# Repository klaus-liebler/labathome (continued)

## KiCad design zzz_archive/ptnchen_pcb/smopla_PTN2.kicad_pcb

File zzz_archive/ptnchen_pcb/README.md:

# smopla_PTN2 - "Das kleine Peteh Ennchen"

Der kleine Bruder von lab@home. Ermöglicht das Experimentieren mit PT1...PTn-Gliedern, die intern als RC-Kombination (entkoppelt über Operationsverstärker) ausgeführt sind.
Features:
- Drei hintereinander geschaltete RC-Glieder, die bekanntlich PT1-Verhalten aufweisen; bilden eine Regelstrecke
- WIFI-fähiger Microcontroller (ESP32)
- Webbasierte Schnittstelle
- bald: Schnittstelle zu WinFACT Boris über WiFi
- Anregung über mechanischen Schalter oder softwaregesteurert über den Microcontroller
- Jedes PT1-Glied kann mit einstellbarer Intensität gestört werden
- Technisch: Anregungsspannung und Spannungen am Ausgang der RC-Glieder über Laborstecker herausgeführt und auf Analog-Digital-Wandler geführt
- Fachlich: Spannungen sind über externe Messinstrumente messbar oder stehen auf der Weboberfläche zur Verfügung oder stehen in einem BORIS-Funktionsbaustein zur Verfügung
- Softwareseitig kann der Regelkreis geöffnet oder geschlossen werden. Es stehen verschiedene Reglertypen und Parametersets zur Verfügung
- Die Verstärker zur Entkopplung der PT1-Glieder lassen sich mechanisch aktivieren und deaktivieren (dann keine Rückkopplungsfreiheit)
- Farbige LEDs zeigen den Zustand des Gesamtsystems und der einzelnen PT1-Glieder an
- Spannungsversorgung, Programmierung und bei Bedarf auch Kommunikation über USB-C

Ein Bild der Baugruppe sagt mehr, als tausend Worte

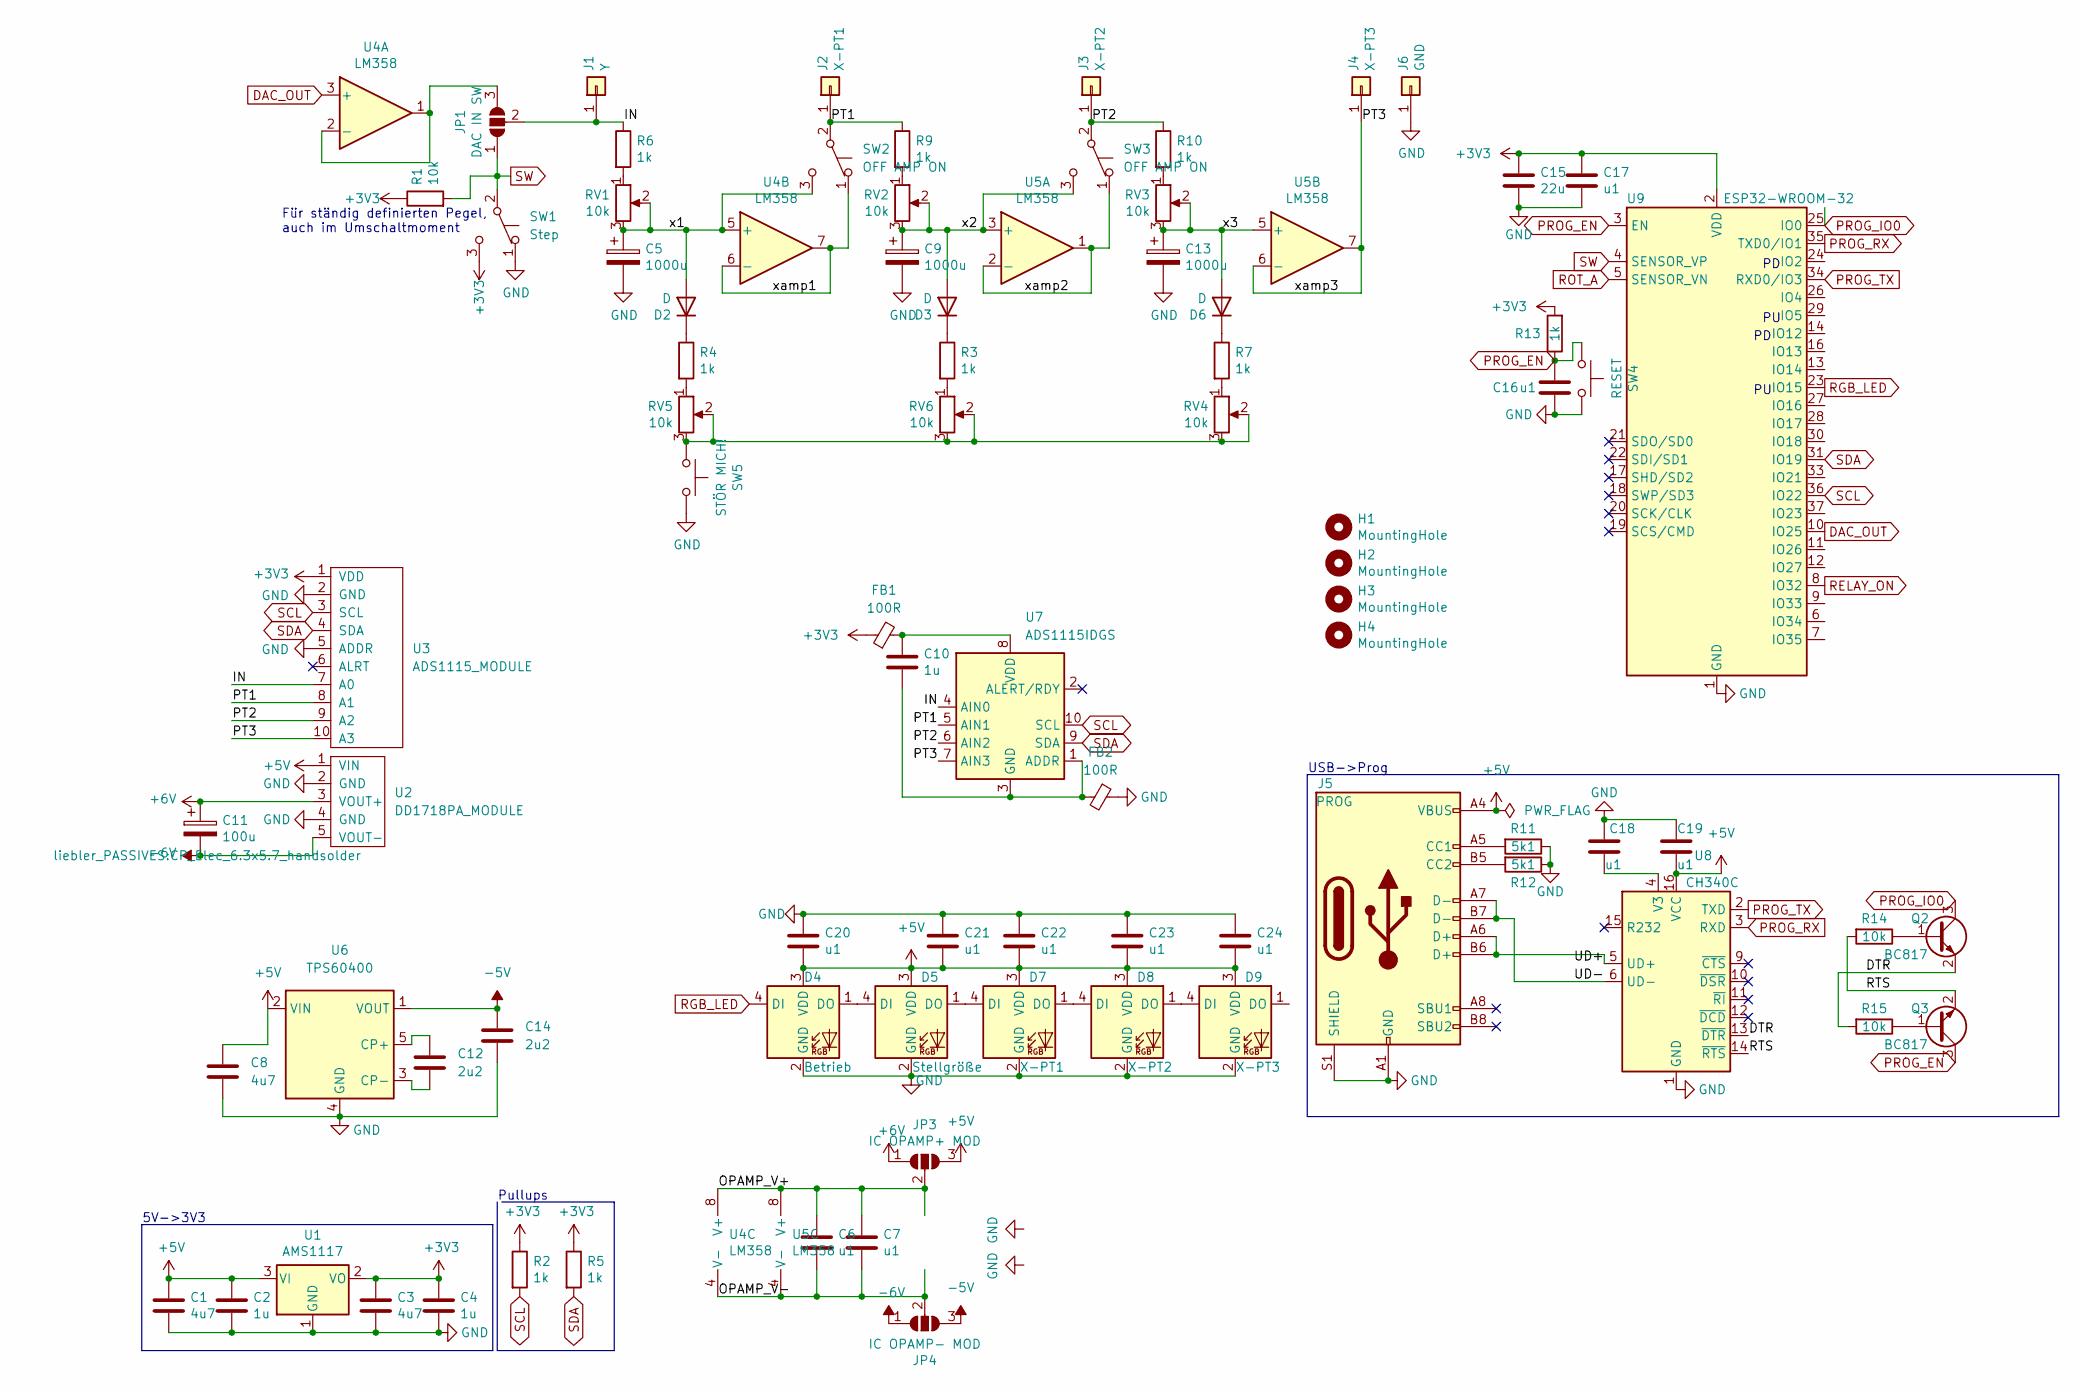
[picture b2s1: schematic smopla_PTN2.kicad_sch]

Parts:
C1, C3, C8: 4u7; C_0805_2012Metric_Pad1.18x1.45mm_HandSolder
C2, C4, C10: 1u; C_0805_2012Metric_Pad1.18x1.45mm_HandSolder
C5, C9, C13: 1000u; CP_Elec_10x10_handsolder; JLCPCB C280409
C6, C7, C16, C17, C18, C19, C20, C21, C22, C23, C24: u1; C_0805_2012Metric_Pad1.18x1.45mm_HandSolder
C11: 100u; CP_Elec_6.3x5.7_handsolder
C12, C14: 2u2; C_0805_2012Metric_Pad1.18x1.45mm_HandSolder
C15: 22u; C_0805_2012Metric_Pad1.18x1.45mm_HandSolder
D2, D3, D6: D; D_SOD-123_handsolder
D4: Betrieb; LED_D5.0mm-4_RGB_Staggered_Pins
D5: Stellgröße; LED_D5.0mm-4_RGB_Staggered_Pins
D7: X-PT1; LED_D5.0mm-4_RGB_Staggered_Pins
D8: X-PT2; LED_D5.0mm-4_RGB_Staggered_Pins
D9: X-PT3; LED_D5.0mm-4_RGB_Staggered_Pins
FB1, FB2: 100R; L_0805_2012Metric_Pad1.05x1.20mm_HandSolder
H1, H2, H3, H4: MountingHole; MountingHole_3.2mm_M3_DIN965
J1: Y; Banana_RECESSED
J2: X-PT1; Banana_RECESSED
J3: X-PT2; Banana_RECESSED
J4: X-PT3; Banana_RECESSED
J5: PROG; USB_C_Receptacle_HRO_TYPE-C-31-M-12_IMPROVED
J6: GND; Banana_RECESSED
JP1: DAC IN SW; SolderJumper-3_P1.3mm_Open_RoundedPad1.0x1.5mm_NumberLabels
JP3: IC OPAMP+ MOD; SolderJumper-3_P1.3mm_Open_RoundedPad1.0x1.5mm_NumberLabels
JP4: IC OPAMP- MOD; SolderJumper-3_P1.3mm_Open_RoundedPad1.0x1.5mm_NumberLabels
Q2, Q3: BC817; SOT-23_Handsoldering
R1, R14, R15: 10k; R_0805_2012Metric_Pad1.20x1.40mm_HandSolder
R2, R3, R4, R5, R6, R7, R9, R10, R13: 1k; R_0805_2012Metric_Pad1.20x1.40mm_HandSolder
R11, R12: 5k1; R_0805_2012Metric_Pad1.20x1.40mm_HandSolder
RV1, RV2, RV3: 10k; Potentiometer_Alps_RK09K_Single_Vertical
RV4, RV5, RV6: 10k; Potentiometer_Bourns_3386P_Vertical
SW1: Step; MTS-102_recessed
SW2, SW3: OFF AMP ON; Switch_SS12D00
SW4: RESET; SW_SPST_TL3342
SW5: STÖR MICH!; Button_12mm_ANCHOR_CENTER
U1: AMS1117; SOT-223-3_TabPin2_HANDSOLDER
U2: DD1718PA_MODULE; DD1718PA_MODULE_SMD
U3: ADS1115_MODULE; ADS1115_MODULE_SMD
U4, U5: LM358; SOIC-8_3.9x4.9mm_Pitch1.27mm_handsolder
U6: TPS60400; SOT-23-5
U7: ADS1115IDGS; TSSOP-10_3x3mm_P0.5mm
U8: CH340C; SOIC-16_3.9x9.9mm_P1.27mm
U9: ESP32-WROOM-32

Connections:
+3V3: C3.2, C4.1, C15.1, C17.2, FB1.1, R1.1, R2.1, R5.1, R13.2, SW1.3 (C), U1.2 (VO), U3.1 (VDD), U9.2 (VDD)
+5V: C1.2, C2.1, C8.1, C19.1, C20.2, C21.2, C22.2, C23.2, C24.2, D4.3 (VDD), D5.3 (VDD), D7.3 (VDD), D8.3 (VDD), D9.3 (VDD), J5.A4 (VBUS), J5.A9 (VBUS), J5.B4 (VBUS), J5.B9 (VBUS), JP3.3 (B), U1.3 (VI), U2.1 (VIN), U6.2 (VIN), U8.16 (VCC)
+6V: C11.1, JP3.1 (A), U2.3 (VOUT+)
-5V: C14.1, JP4.3 (B), U6.1 (VOUT)
-6V: C11.2, JP4.1 (A), U2.5 (VOUT-)
/DTR: Q2.2 (E), R15.2, U8.13 (~DTR)
/IN: J1.1, JP1.2 (C), R6.1, U3.7 (A0), U7.4 (AIN0)
/OPAMP_V+: C6.1, C7.1, JP3.2 (C), U4.8 (V+), U5.8 (V+)
/OPAMP_V-: C6.2, C7.2, JP4.2 (C), U4.4 (V-), U5.4 (V-)
/PT1: J2.1, R9.1, SW2.2 (B), U3.8 (A1), U7.5 (AIN1)
/PT2: J3.1, R10.1, SW3.2 (B), U3.9 (A2), U7.6 (AIN2)
/PT3: J4.1, U3.10 (A3), U5.6 (-), U5.7, U7.7 (AIN3)
/RTS: Q3.2 (E), R14.2, U8.14 (~RTS)
/UD+: J5.A6 (D+), J5.B6 (D+), U8.5 (UD+)
/UD-: J5.A7 (D-), J5.B7 (D-), U8.6 (UD-)
/x1: C5.1, D2.2 (A), RV1.2, RV1.3, SW2.3 (C), U4.5 (+)
/x2: C9.1, D3.2 (A), RV2.2, RV2.3, SW3.3 (C), U5.3 (+)
/x3: C13.1, D6.2 (A), RV3.2, RV3.3, U5.5 (+)
/xamp1: SW2.1 (A), U4.6 (-), U4.7
/xamp2: SW3.1 (A), U5.1, U5.2 (-)
DAC_OUT: U4.3 (+), U9.10 (IO25)
GND: C1.1, C2.2, C3.1, C4.2, C5.2, C8.2, C9.2, C13.2, C14.2, C15.2, C16.1, C17.1, C18.2, C19.2, C20.1, C21.1, C22.1, C23.1, C24.1, D4.2 (GND), D5.2 (GND), D7.2 (GND), D8.2 (GND), D9.2 (GND), FB2.1, J5.A1 (GND), J5.A12 (GND), J5.B1 (GND), J5.B12 (GND), J5.S1 (SHIELD), J6.1, R11.1, R12.1, SW1.1 (A), SW4.2, SW5.2, U1.1 (GND), U2.2 (GND), U2.4 (GND), U3.2 (GND), U3.5 (ADDR), U6.4 (GND), U8.1 (GND), U9.1 (GND), U9.15 (GND), U9.38 (GND), U9.39 (GND)
unnamed: C10.1, FB2.2, U7.1 (ADDR), U7.3 (GND)
unnamed: C10.2, FB1.2, U7.8 (VDD)
unnamed: C12.1, U6.5 (CP+)
unnamed: C12.2, U6.3 (CP-)
unnamed: C18.1, U8.4 (V3)
unnamed: D2.1 (K), R4.1
unnamed: D3.1 (K), R3.1
unnamed: D4.1 (DO), D5.4 (DI)
unnamed: D5.1 (DO), D7.4 (DI)
unnamed: D6.1 (K), R7.1
unnamed: D7.1 (DO), D8.4 (DI)
unnamed: D8.1 (DO), D9.4 (DI)
unnamed: J5.A5 (CC1), R11.2
unnamed: J5.B5 (CC2), R12.2
unnamed: JP1.3 (B), U4.1, U4.2 (-)
unnamed: Q2.1 (B), R14.1
unnamed: Q3.1 (B), R15.1
unnamed: R3.2, RV6.1
unnamed: R4.2, RV5.1
unnamed: R6.2, RV1.1
unnamed: R7.2, RV4.1
unnamed: R9.2, RV2.1
unnamed: R10.2, RV3.1
unnamed: RV4.2, RV4.3, RV5.2, RV5.3, RV6.2, RV6.3, SW5.1
PROG_EN: C16.2, Q3.3 (C), R13.1, SW4.1, U9.3 (EN)
PROG_IO0: Q2.3 (C), U9.25 (IO0)
PROG_RX: U8.3 (RXD), U9.35 (TXD0/IO1)
PROG_TX: U8.2 (TXD), U9.34 (RXD0/IO3)
RELAY_ON: U9.8 (IO32)
RGB_LED: D4.4 (DI), U9.23 (IO15)
ROT_A: U9.5 (SENSOR_VN)
SCL: R2.2, U3.3 (SCL), U7.10 (SCL), U9.36 (IO22)
SDA: R5.2, U3.4 (SDA), U7.9 (SDA), U9.31 (IO19)
SW: JP1.1 (A), R1.2, SW1.2 (B), U9.4 (SENSOR_VP)

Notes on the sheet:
USB->Prog
Für ständig definierten Pegel, auch im Umschaltmoment
5V->3V3
Pullups

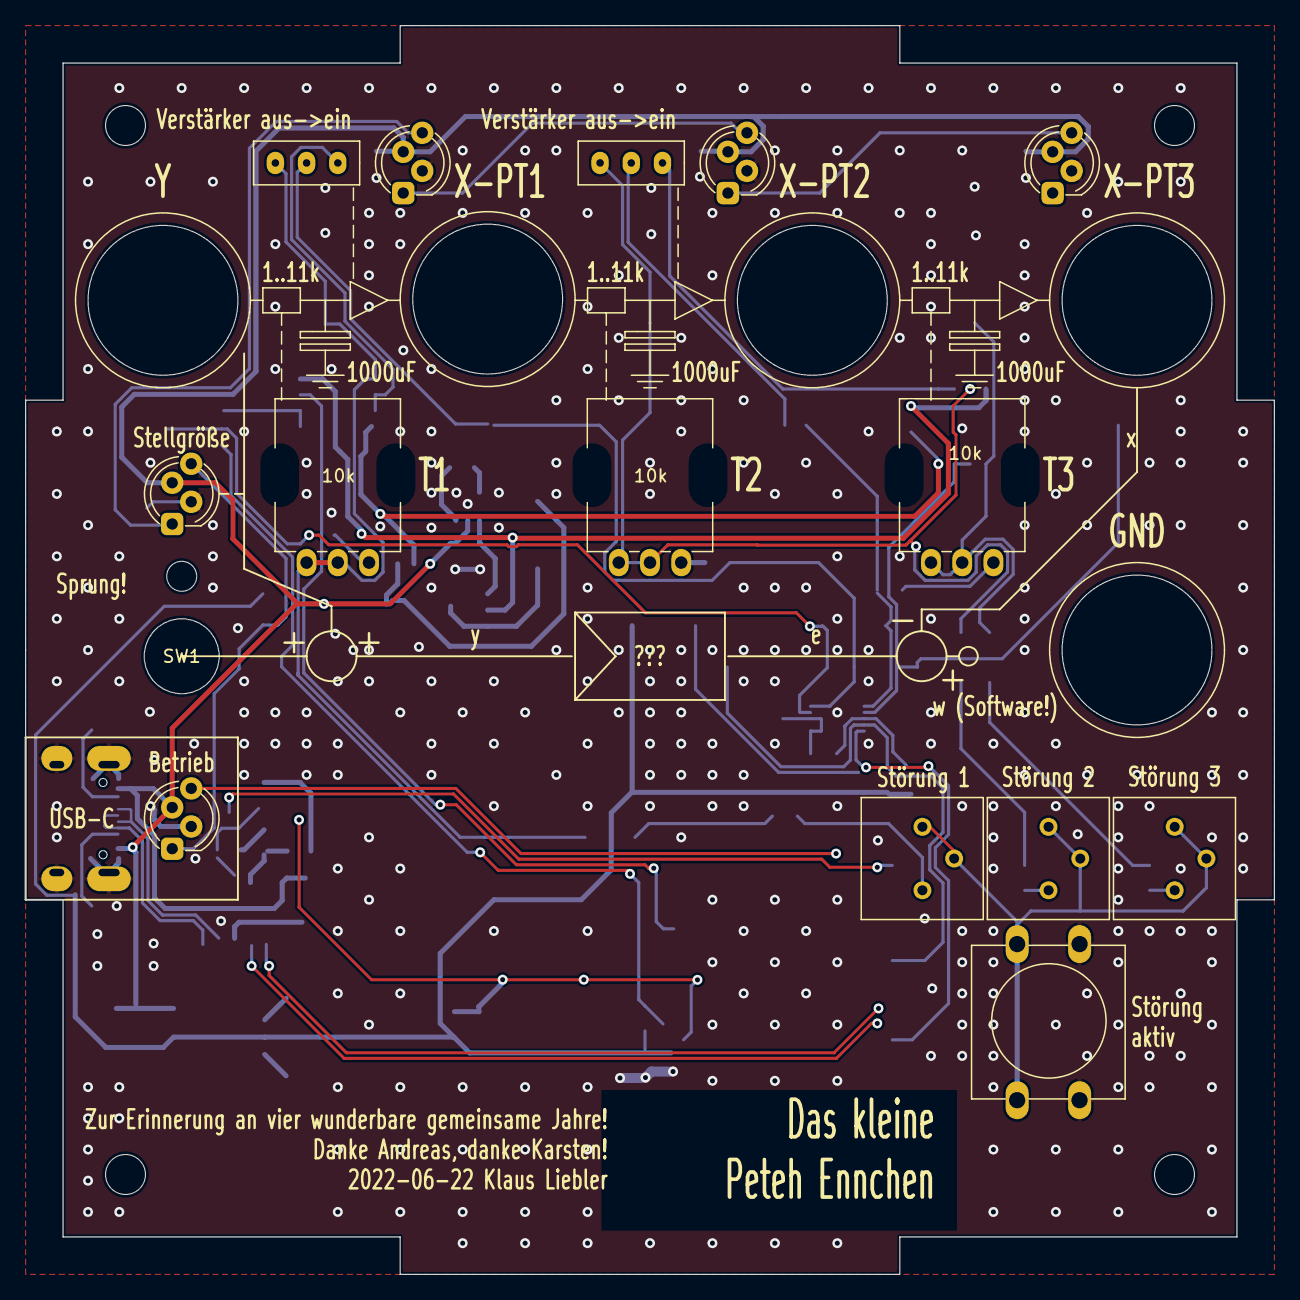
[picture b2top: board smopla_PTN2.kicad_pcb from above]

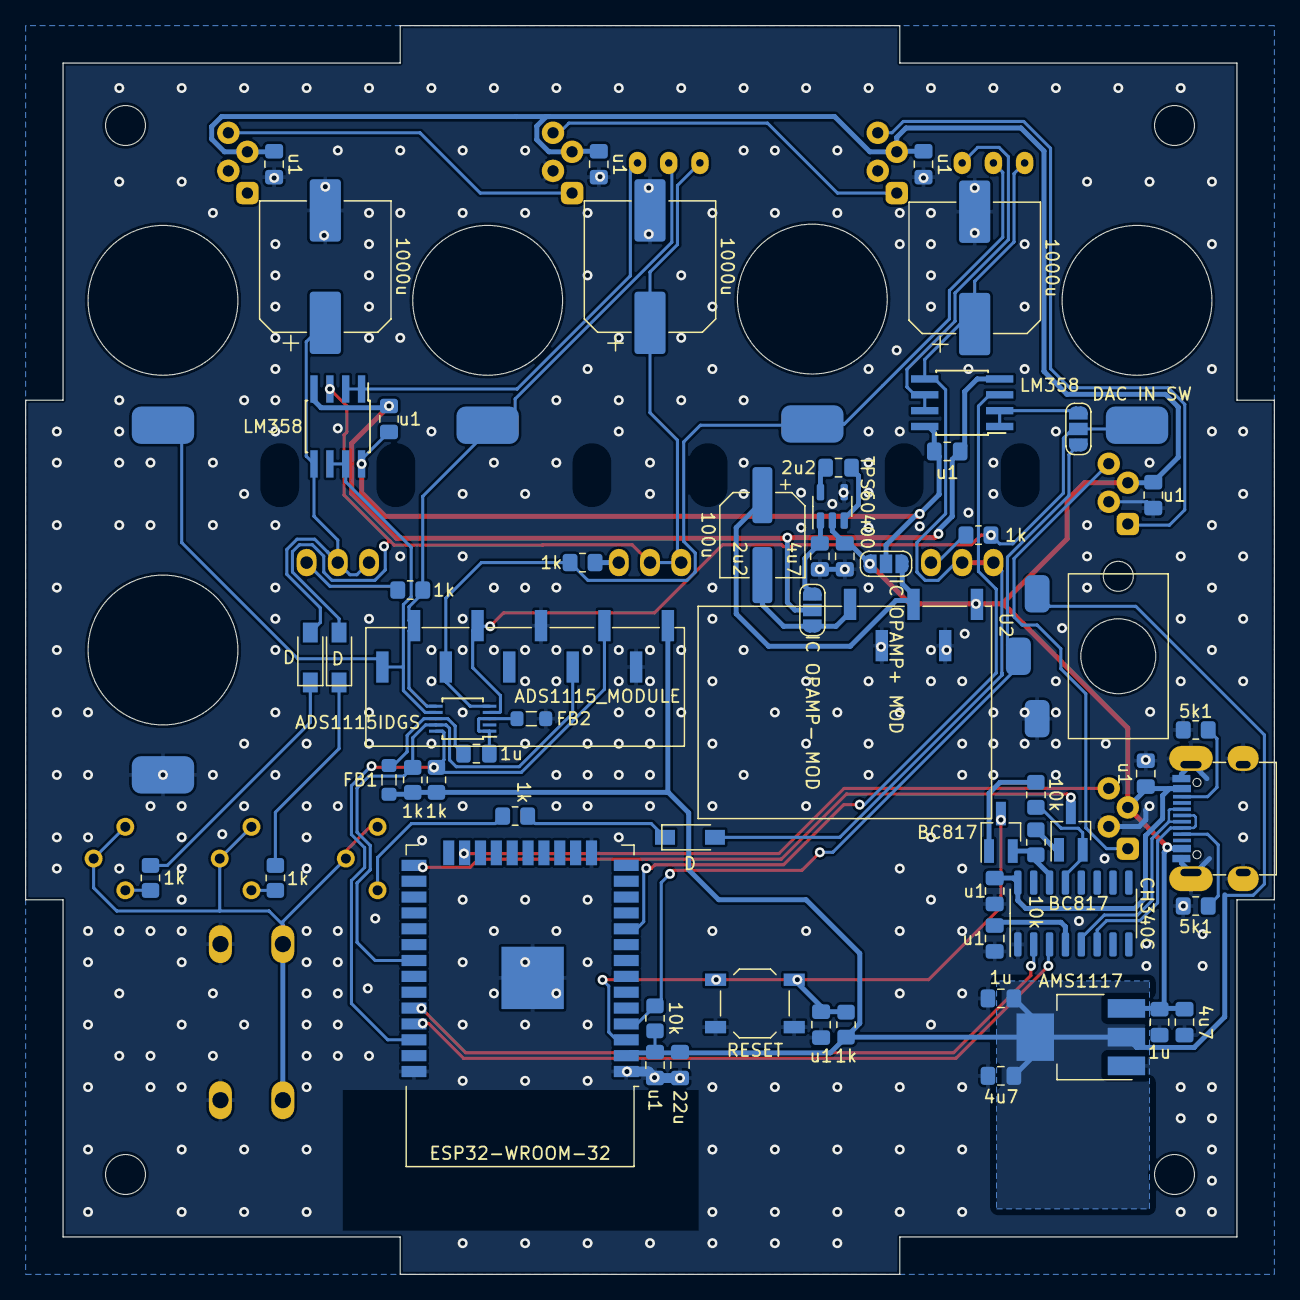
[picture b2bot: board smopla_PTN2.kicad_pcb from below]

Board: 2 copper layers, 100.0 x 100.0 mm, 83 parts (59 on the bottom side), 54 nets.

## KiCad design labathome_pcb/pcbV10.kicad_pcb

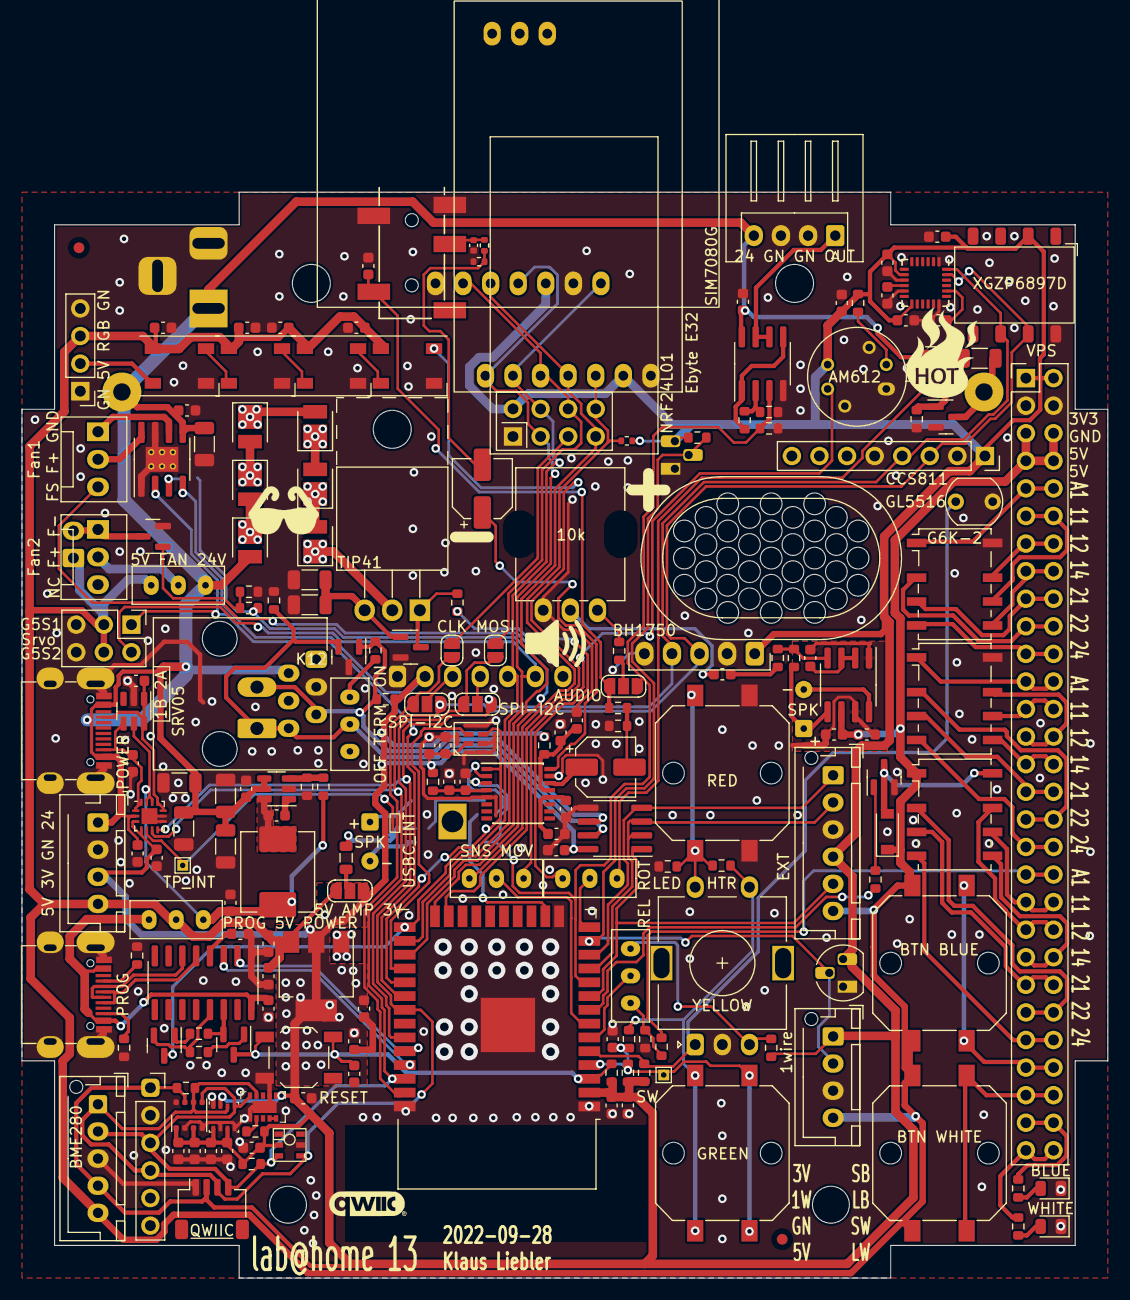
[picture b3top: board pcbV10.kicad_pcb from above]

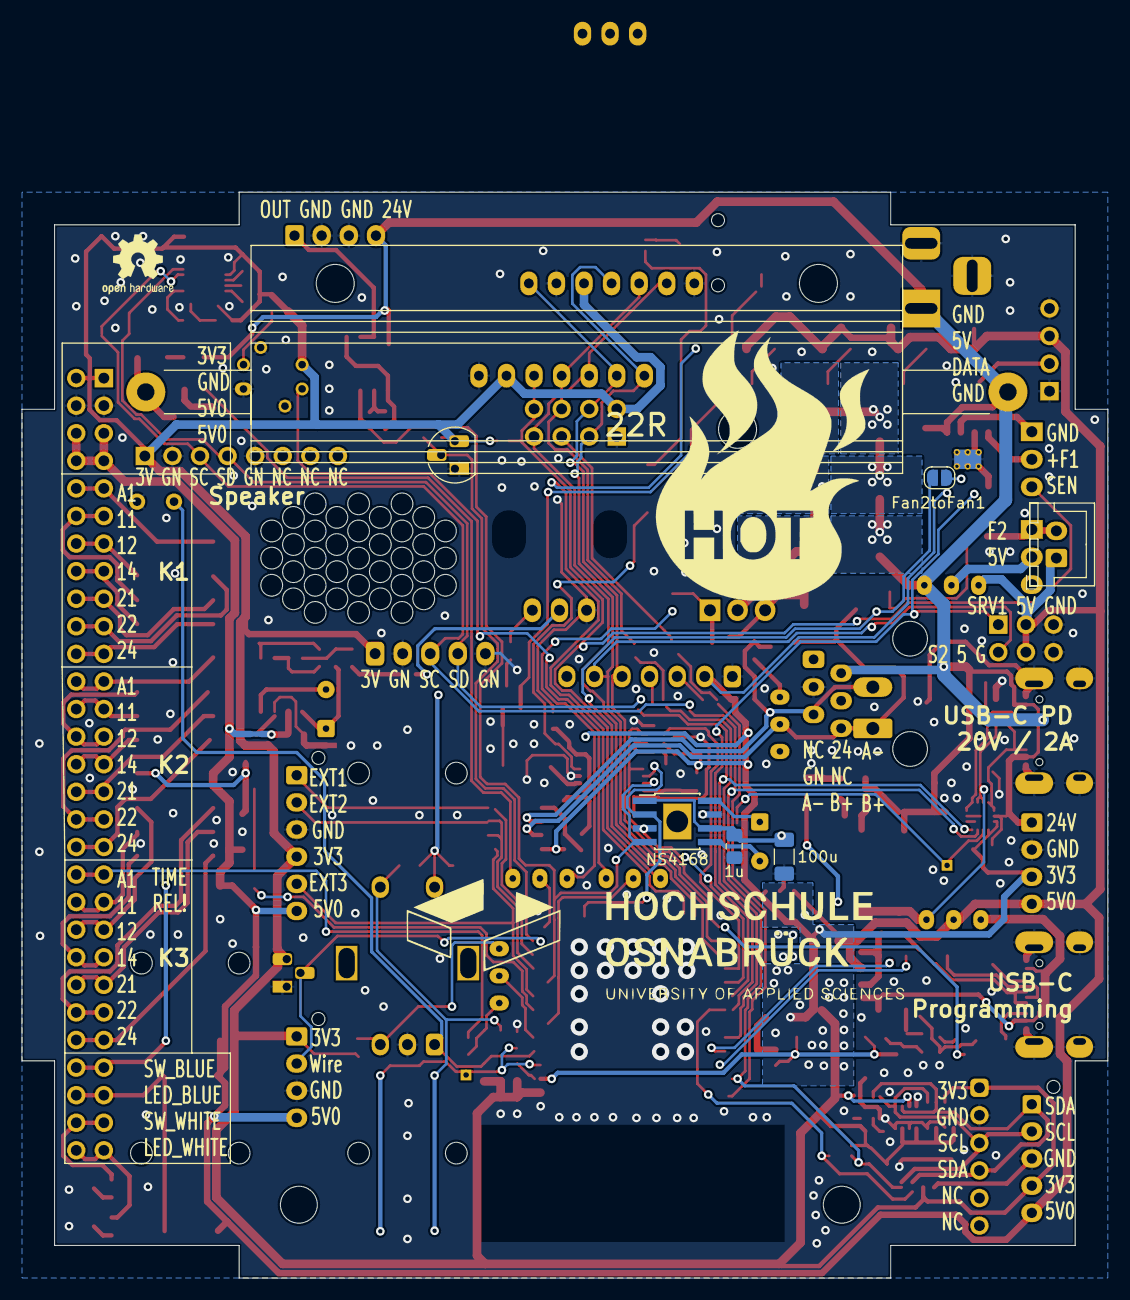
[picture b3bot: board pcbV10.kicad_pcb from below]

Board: 2 copper layers, 100.0 x 100.0 mm, 221 parts (12 on the bottom side), 144 nets.

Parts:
C1, C8: 4u7; C_0603_1608Metric
C2, C36, C47: 22u; C_0603_1608Metric
C3, C9, C23, C38: 1u; C_0603_1608Metric
C4, C5, C6, C7, C10, C11, C12, C14, C15, C16, C18, C19, C20, C24, C25, C28, C29, C30, C31, C32, C33, C35, C37, C40, C42, C44, C51, C52, C54, C55: u1; C_0603_1608Metric
C13, C43: 47u; C_0603_1608Metric
C17, C58: 1u; C_1206_3216Metric
C21: 1u; C_0805_2012Metric_Pad1.18x1.45mm_HandSolder
C22, C27, C60: 10u; C_1206_3216Metric
C26, C39, C61: 10u; C_0603_1608Metric
C34: 100u; C_1206_3216Metric_Pad1.33x1.80mm_HandSolder
C45, C46: 47u; CP_Elec_5x5.4
C48, C50: 10n; C_0603_1608Metric
C49: 10n; C_0402_1005Metric
C53: 2n2; C_0603_1608Metric
C56, C57: n33; C_0603_1608Metric
D1, D2, D3, D15: WS2812B; LED_WS2812B_PLCC4_5.0x5.0mm_P3.2mm
D4: PSM712; SOT-23
D5: 1N4007; D_SOD-123
D6: HTR ON; LED_0805_2012Metric
D7: WHITE; D_0805_2012Metric
D8: BLUE; D_0805_2012Metric
D9, D10, D11, D12, D13, D14: WHITE; LED_PLCC_2835
FB1: 100R; L_0805_2012Metric
FID1, FID2: Fiducial; Fiducial_1mm_Mask2mm
IMG1: Speaker; speaker
IMG2: Augenschutz; googles
IMG4: FHOS; LOGO_FHOS_80mm
IMG5: QR-CODE; QR_CODE_smopla_de
IMG6: OPEN Hardware; OSHW-Logo2_7.3x6mm_SilkScreen
IMG7: HOT; hot
IMG8: HOT_BIG; hot_big
IMG9: Augenschutz; qwiic
J1: PROG; USB_C_Receptacle_HRO_TYPE-C-31-M-12_IMPROVED
J2: Srvo; PinHeader_2x03_P2.54mm_Vertical
J3: I2C; JST_XH_B5B-XH-AM_1x05_P2.50mm_Vertical
J4: 1wire; JST_XH_B4B-XH-AM_1x04_P2.50mm_Vertical
J5: EXT; JST_XH_B6B-XH-AM_1x06_P2.50mm_Vertical
J6: 5V 3V GN 24; JST_XH_B4B-XH-AM_1x04_P2.50mm_Vertical
J7: 485; WR_MJ_Modular_Jack_Vertical_Plastic_6P6C
J8: POWER; USB_C_Receptacle_HRO_TYPE-C-31-M-12_IMPROVED
J9: GN 5V RGB GN; PinHeader_1x04_P2.54mm_Vertical
J10: Fan1; FanPinHeader_1x03_P2.54mm_Vertical
J11: Fan2; FanPinHeader_1x03_P2.54mm_Vertical
J12: VPS; PinHeader_2x29_P2.54mm_Vertical
J13, J19: SPK; SolderWire-0.1sqmm_1x02_P3.6mm_D0.4mm_OD1mm
J15: 1B 2A; PhoenixContact_MCV_1,5_2-G-3.81_1x02_P3.81mm_Vertical
J16: BME280; PinSocket_1x06_P2.54mm_Vertical
J17: CCS811; PinSocket_1x08_P2.54mm_Vertical
J18: Power; BarrelJack_Horizontal
J20: FAN5V; JST_XH_B2B-XH-A_1x02_P2.50mm_Vertical
J21: QWIIC; JST_SH_SM04B-SRSS-TB_1x04-1MP_P1.00mm_Horizontal
J22: AudioJack3_SwitchT; PJ-327A
J24: 24 GN GN OUT; JST_XH_S4B-XH-A_1x04_P2.50mm_Horizontal
JP1: AUDIO; SolderJumper-3_P1.3mm_Open_RoundedPad1.0x1.5mm_NumberLabels
JP2: USBC_INT; Jumper_Trace_025x150x015
JP3, JP4: SPI-I2C; SolderJumper-3_P1.3mm_Open_RoundedPad1.0x1.5mm_NumberLabels
JP5: 5V AMP 3V; SolderJumper-3_P1.3mm_Open_RoundedPad1.0x1.5mm_NumberLabels
JP6: MOSI; SolderJumper-2_P1.3mm_Open_RoundedPad1.0x1.5mm
JP7: CLK; SolderJumper-2_P1.3mm_Open_RoundedPad1.0x1.5mm
JP8: Fan2toFan1; SolderJumper-2_P1.3mm_Open_RoundedPad1.0x1.5mm
K1, K2, K3: G6K-2; Relay_DPDT_Omron_G6K-2F-Y
L2: 4u7; L_Abracon_ASPI-0630LR
NT1, NT2: 1; NetTie-2_SMD_Pad0.5mm
Q1, Q2, Q4, Q6: BC817; SOT-23
Q5, Q9: IRLML6344; SOT-23
Q7: TIP41; TO-220-3_Horizontal_TabUp
R1, R4, R11, R12, R14, R15, R17, R23, R26, R34, R36, R44: 1k; R_0603_1608Metric
R2, R3: 5k1; R_0603_1608Metric
R5, R8, R21, R28: 4k7; R_0603_1608Metric
R6, R7, R16, R35, R37, R38, R51, R52: 10k; R_0603_1608Metric
R9: GL5516; R_LDR_5.1x4.3mm_P3.4mm_Vertical
R10: 10k; R_0402_1005Metric
R13: K12; R_0603_1608Metric
R18: 22R; Resistor_100W
R19: 3k3; R_1206_3216Metric
R20, R39, R53: 22k; R_0603_1608Metric
R22, R30: 2k2; R_0603_1608Metric
R24, R25, R49: k1; R_0603_1608Metric
R32, R33: 10R; R_1206_3216Metric
R40, R42: 1R; R_0603_1608Metric
R43: M22; R_0603_1608Metric
R45: 13k; R_0603_1608Metric
R46: 68k; R_0603_1608Metric
R48: M22; R_0402_1005Metric
R50: k1; R_0402_1005Metric
R54: 1M; R_0603_1608Metric
RV1: 10k; Potentiometer_Alps_RK09K_Single_Vertical
SP1: Speaker; SPEAKER_2415
SW1: BTN BLUE; SW_Push_1P1T_NO_CK_PTS125Sx43PSMTR
SW2: YELLOW; RotaryEncoder_Alps_EC11E-Switch_Vertical_H20mm
SW3: GREEN; SW_Push_1P1T_NO_CK_PTS125Sx43PSMTR
SW4: RED; SW_Push_1P1T_NO_CK_PTS125Sx43PSMTR
SW5: BTN WHITE; SW_Push_1P1T_NO_CK_PTS125Sx43PSMTR
SW6: OFF TERM ON; Switch_SS12D00
SW7: LED HTR; Switch_SS12D00
SW8: REL ROT; Switch_SS12D00
SW9: SNS MOV; Switch_SS12D00
SW10: 5V FAN 24V; Switch_SS12D00
SW11: PROG 5V POWER; Switch_SS12D00
SW12: RESET; SW_SPST_TL3342
TP1: TP_INT; TestPoint_THTPad_1.0x1.0mm_Drill0.5mm
TP2: SW; TestPoint_THTPad_1.0x1.0mm_Drill0.5mm
U1: AMS1117; SOT-223-3_TabPin2
U2: ESP32-WROOM-32
U3: AHT21
U4: CH340C; SOIC-16_3.9x9.9mm_P1.27mm
U5: UDA1334; SSOP-16_4.4x5.2mm_P0.65mm
U6: MAX3485; SOIC-8_3.9x4.9mm_P1.27mm
U7, U19: DS18B20; TO-92_HandSolder
U8: NRF24L01; nRF24L01_Breakout
U9: RY8310; SOT-23-6
U10: LM358; SOIC-8_3.9x4.9mm_P1.27mm
U11: FUSB302BMPX; WQFN-14-1EP_2.5x2.5mm_P0.5mm_EP1.45x1.45mm
U12: BME680; Bosch_LGA-8_3x3mm_P0.8mm_ClockwisePinNumbering
U13: BME280; Bosch_LGA-8_2.5x2.5mm_P0.65mm_ClockwisePinNumbering
U14: IPS_240_240; IPS_240_240_1.3
U15: CCS811; AMS_LGA-10-1EP_2.7x4mm_P0.6mm
U16: AS4950; SOIC-8-1EP_3.9x4.9mm_P1.27mm_EP2.29x3mm_ThermalVias
U18: MD8002A; SOIC-8_3.9x4.9mm_P1.27mm
U20: BH1750; GY-302
U22: AM612
U23: MPU-6050; InvenSense_QFN-24_4x4mm_P0.5mm
U24: SRV05; SOT-23-6
U25: NS4168; SOIC-8_3.9x4.9mm_Pitch1.27mm_pad_handsolder
U26: MSM261D4030H1CPM
X1: FAN_6024
X2: XGZP6897D
X3: Ebyte E32; Ebyte-E32-900T20D
X4: SIM7080G; SIM7080G_AND_MODULE

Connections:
1wire: J4.2, R4.1, U2.13 (IO14), U7.2 (DQ), U19.2 (DQ)
485_DE: J5.2, U2.11 (IO26), U6.2 (~RE), U6.3 (DE)
485_DI: J5.1, U2.12 (IO27), U6.4 (DI)
485_RO: J5.5, U2.9 (IO33), U6.1 (RO)
+3V3: C2.1, C4.2, C8.2, C9.1, C12.2, C15.2, C19.2, C28.2, C29.2, C30.2, C31.2, C37.2, C38.1, C39.2, C50.2, C52.2, C55.2, C61.1, J3.4, J4.1, J5.4, J6.3, J12.1, J12.2, J16.1, J17.1, J21.2, JP5.3 (B), R1.2, R4.2, R5.2, R8.2, R10.1, R12.1, R17.2, R20.1, R28.2, R40.2, R42.2, R44.1, R54.1, U1.2 (VO), U2.2 (VDD), U3.2 (VDD), U6.8 (VCC), U7.3 (VDD), U8.2 (VCC), U11.3 (VDD), U11.4 (VDD), U12.2 (CSB), U12.6 (VDDIO), U12.8 (VDD), U13.2 (CSB), U13.6 (VDDIO), U13.8 (VDD), U14.2 (VCC), U15.6 (VDD), U16.4 (Vref), U19.3 (VDD), U20.1 (VCC), U22.4 (VDD), U23.8 (VDDIO), U23.13 (VDD), U26.1 (VDD), X2.2 (VDD), X3.6 (VCC), X4.5 (V-VCC)
+5P: C6.1, J1.A4 (VBUS), J1.A9 (VBUS), J1.B4 (VBUS), J1.B9 (VBUS), SW11.3 (C), U4.16 (VCC)
+5V: C1.2, C3.1, C7.2, C14.2, C16.2, C18.2, D1.1 (VDD), D2.1 (VDD), D3.1 (VDD), D5.1 (K), D15.1 (VDD), J2.3, J2.4, J3.5, J4.4, J5.6, J6.4, J9.3, J12.5, J12.6, J12.7, J12.8, J20.1, JP5.1 (A), K3.1, NT1.2, SW1.1, SW5.1, SW10.1 (A), SW11.2 (B), U1.3 (VI)
+5VA: C25.1, C26.1, NT1.1, U18.6 (VDD)
+24V: C17.1, C22.2, C27.2, C32.2, C33.2, C40.2, C54.2, C58.1, C60.2, D6.2 (A), D14.2 (A), J6.1, J7.2, J8.A4 (VBUS), J8.A9 (VBUS), J8.B4 (VBUS), J8.B9 (VBUS), J18.1, J24.4, R18.1, SW10.3 (C), U9.4 (~SHDN), U9.5 (VIN), U10.8 (V+), U11.2 (VBUS), U16.5 (VP)
/C: JP3.2 (C), U14.3 (SCL)
/D: JP4.2 (C), U14.4 (SDA)
/D9_COOL: D9.1 (K), Q7.2 (C)
/D10_COOL: D10.1 (K), D11.2 (A)
/D11_COOL: D11.1 (K), D13.2 (A)
/D12_COOL: D10.2 (A), D12.1 (K)
/D13_COOL: D9.2 (A), D13.1 (K)
/D14_COOL: D12.2 (A), D14.1 (K)
/DTR: Q2.2 (E), R6.2, U4.13 (~DTR)
/RTS: Q1.2 (E), R7.2, U4.14 (~RTS)
/UD+: J1.A6 (D+), J1.B6 (D+), U4.5 (UD+)
/UD-: J1.A7 (D-), J1.B7 (D-), U4.6 (UD-)
/VFAN: J11.2, SW10.2 (B)
/analog_amp/LEFT: C48.1, J22.T, JP1.3 (B), R49.2
/analog_amp/RIGHT: C49.2, J22.R, R50.2
/analog_amp/SPK+: J13.1, R39.1, U18.5 (VO1)
/analog_amp/SPK-: J13.2, U18.8 (VO2)
/analog_amp/VoN: J19.2, U25.5 (VoN)
/analog_amp/VoP: J19.1, U25.8 (VoP)
/psu/5Vx: C36.1, L2.1, R46.1, SW11.1 (A), U11.12 (VCONN), U11.13 (VCONN), U24.5 (VP)
/psu/CC1: C56.2, J8.A5 (CC1), U11.10 (CC1), U11.11 (CC1), U24.1 (IO1), U24.6 (IO4)
/psu/CC2: C57.2, J8.B5 (CC2), U11.1 (CC2), U11.14 (CC2), U24.4 (IO3)
/psu/SW: C35.2, L2.2, U9.6 (SW)
AUDIO: JP1.1 (A), R52.2, U2.10 (IO25), U5.3 (DATAI), U10.3 (+), U25.4 (SDATA)
FAN1_DRIVE: J2.1, U2.30 (IO18), U16.2 (IN2)
FAN1_SENSE: J10.3, R10.2, SW9.3 (C), U8.8 (IRQ), X3.5 (AUX)
FAN2_DRIVE: JP8.1 (A), R34.2, U2.24 (IO2)
GND: C1.1, C2.2, C3.2, C4.1, C5.1, C6.2, C7.1, C8.1, C9.2, C10.2, C11.1, C12.1, C13.1, C14.1, C15.1, C16.1, C17.2, C18.1, C19.1, C20.1, C21.2, C22.1, C27.1, C28.1, C29.1, C30.1, C31.1, C32.1, C33.1, C34.2, C36.2, C37.1, C38.2, C39.1, C40.1, C42.1, C43.1, C44.1, C47.1, C48.2, C49.1, C50.1, C51.1, C52.1, C53.1, C54.1, C55.1, C56.1, C57.1, C58.2, C60.1, C61.2, D1.3 (VSS), D2.3 (VSS), D3.3 (VSS), D4.3 (A), D7.1 (K), D8.1 (K), D15.3 (VSS), J1.A1 (GND), J1.A12 (GND), J1.B1 (GND), J1.B12 (GND), J1.S1 (SHIELD), J2.5, J2.6, J3.3, J4.3, J5.3, J6.2, J7.3, J8.A1 (GND), J8.A12 (GND), J8.B1 (GND), J8.B12 (GND), J8.S1 (SHIELD), J9.1, J9.4, J12.3, J12.4, J16.2, J17.2, J17.5, J18.2, J18.3, J21.1, J22.S, J24.2, J24.3, K1.8, K2.8, NT2.1, Q4.2 (E), Q5.2 (S), Q6.2 (E), Q9.2 (S), R2.1, R3.1, R9.2, R11.2, R16.1, R23.1, R32.2, R33.2, R35.1, R36.1, R43.2, R45.1, R48.1, R51.1, R52.1, RV1.3, SW2.C, SW4.1, SW12.2, U1.1 (GND), U2.1 (GND), U2.15 (GND), U2.38 (GND), U2.39 (GND), U3.5 (GND), U4.1 (GND), U5.5 (VSSD), U5.15 (VSSA), U6.5 (GND), U7.1 (GND), U8.1 (GND), U9.2 (GND), U10.4 (V-), U11.8 (GND), U11.9 (GND), U11.15 (GND), U12.1 (GND), U12.5 (SDO), U12.7 (GND), U13.1 (GND), U13.5 (SDO), U13.7 (GND), U14.1 (GND), U15.1 (ADDR), U15.7 (~WAKE), U15.11 (GND), U16.1 (GND), U16.7 (LSEN), U16.9 (PAD), U19.1 (GND), U20.2 (GND), U20.5 (ADDR), U22.1 (SENS), U22.3 (VSS_GND), U22.6 (TIME), U23.1 (CLKIN), U23.9 (AD0), U23.11 (FSYNC), U23.18 (GND), U24.2 (VN), U25.7 (GND), U26.2 (LR), U26.5 (GND), U26.6 (GND), U26.7 (GND), U26.8 (GND), X2.8 (GND), X3.7 (GND), X4.1 (G-GND), X4.6 (G-GND)
GNDA: C23.2, C25.2, C26.2, NT2.2, U18.1 (SD), U18.7 (GND)
HEATER: R15.2, SW7.1 (A)
HEATER_LED: SW7.2 (B), U2.14 (IO12)
I2S_SCK: U2.29 (IO5), U5.1 (BCK), U25.3 (BCLK), U26.3 (CLK)
I2S_SD: U2.28 (IO17), U26.4 (DATA)
I2S_WS: U2.16 (IO13), U5.2 (WS), U25.2 (LRCLK)
I34: SW8.2 (B), U2.6 (IO34)
I35: SW9.2 (B), U2.7 (IO35)
K1_11: J12.11, J12.12, K1.6
K1_12: J12.13, J12.14, K1.7
K1_14: J12.15, J12.16, K1.5
K1_21: J12.17, J12.18, K1.3
K1_22: J12.19, J12.20, K1.2
K1_24: J12.21, J12.22, K1.4
K1_A1: J12.9, J12.10, K1.1
K2_11: J12.25, J12.26, K2.6
K2_12: J12.27, J12.28, K2.7
K2_14: J12.29, J12.30, K2.5
K2_21: J12.31, J12.32, K2.3
K2_22: J12.33, J12.34, K2.2
K2_24: J12.35, J12.36, K2.4
K2_A1: J12.23, J12.24, K2.1
K3_11: J12.39, J12.40, K3.6
K3_12: J12.41, J12.42, K3.7
K3_14: J12.43, J12.44, K3.5
K3_21: J12.45, J12.46, K3.3
K3_22: J12.47, J12.48, K3.2
K3_24: J12.49, J12.50, K3.4
K3_A1: R36.2, R37.1, SW8.1 (A)
K3_ON: R14.2, U2.8 (IO32)
LED_BLUE: J12.55, J12.56, R25.2
LED_RGB: D1.4 (DIN), U2.23 (IO15)
LED_WHITE: J12.57, J12.58, R24.2
LED_WHITE_P: R26.2, SW7.3 (C)
MOVE: SW9.1 (A), U22.5 (OUT)
unnamed: C10.1, U4.4 (V3)
unnamed: C11.2, C13.2, R40.1, U5.4 (VDDD)
unnamed: C21.1, C34.1, FB1.2, U25.1 (CTRL), U25.6 (VDD)
unnamed: C23.1, U18.2 (BYP), U18.3 (+IN)
unnamed: C24.1, R38.2
unnamed: C24.2, RV1.2
unnamed: C35.1, U9.1 (CB)
unnamed: C42.2, C43.2, R42.1, U5.13 (VDDA)
unnamed: C44.2, C47.2, U5.12 (Vref(DAC))
unnamed: C45.1, U5.14 (VOUTL)
unnamed: C45.2, R43.1, R49.1
unnamed: C46.1, U5.16 (VOUTR)
unnamed: C46.2, R48.2, R50.1
unnamed: C51.2, U23.10 (REGOUT)
unnamed: C53.2, U23.20 (CPOUT)
unnamed: D1.2 (DOUT), D2.4 (DIN)
unnamed: D2.2 (DOUT), D3.4 (DIN)
unnamed: D5.2 (A), K3.8, Q4.3 (C)
unnamed: D6.1 (K), R19.1
unnamed: D7.2 (A), R24.1
unnamed: D8.2 (A), R25.1
unnamed: D15.2 (DOUT), J9.2
unnamed: D3.2 (DOUT), D15.4 (DIN)
unnamed: FB1.1, JP5.2 (C)
unnamed: J1.A5 (CC1), R2.2
unnamed: J1.B5 (CC2), R3.2
unnamed: J10.1, U16.6 (OUT1)
unnamed: J10.2, U16.8 (OUT2)
unnamed: J11.1, J20.2, Q9.3 (D)
unnamed: J12.37, J12.38, R37.2
unnamed: J24.1, U10.6 (-), U10.7
unnamed: JP1.2 (C), R30.1
unnamed: JP2.2 (B), TP1.1, U11.5 (INT_N)
unnamed: JP8.2 (B), U16.3 (IN1)
unnamed: Q1.1 (B), R6.1
unnamed: Q2.1 (B), R7.1
unnamed: Q4.1 (B), R14.1
unnamed: Q5.1 (G), R15.1, R16.2
unnamed: Q5.3 (D), R18.2, R19.2
unnamed: Q6.1 (B), Q7.3 (E), R32.1, R33.1
unnamed: Q6.3 (C), Q7.1 (B), R26.1
unnamed: Q9.1 (G), R34.1, R35.2
unnamed: R13.2, SW6.3 (C)
unnamed: R21.1, R22.2, SW2.S1, SW3.1
unnamed: R22.1, R23.2, SW2.S2, SW4.2
unnamed: R28.1, U15.2 (~RESET)
unnamed: R30.2, RV1.1
unnamed: R38.1, R39.2, U18.4 (-IN)
unnamed: R45.2, R46.2, U9.3 (FB)
unnamed: R51.2, R53.2, U10.2 (-)
unnamed: R53.1, U10.1, U10.5 (+)
unnamed: R54.2, U22.2 (OEN)
unnamed: U15.4 (PWM), U15.5 (Sense)
PROG_EN: C5.2, Q1.3 (C), R1.1, SW12.1, U2.3 (EN)
PROG_IO0: Q2.3 (C), U2.25 (IO0), U8.4 (~CSN), U14.5 (RES), X3.2 (M1), X4.7 (S-SLEEP)
PROG_RX: U2.35 (TXD0/IO1), U4.3 (RXD)
PROG_TX: U2.34 (RXD0/IO3), U4.2 (TXD)
ROT_A: R9.1, R17.1, SW2.A, U2.5 (SENSOR_VN)
ROT_B: R44.2, SW2.B, SW8.3 (C)
RS485A: D4.1 (K), J7.5, J15.2, R12.2, R13.1, U6.6 (A)
RS485B: D4.2 (K), J7.6, J15.1, R11.1, SW6.2 (B), U6.7 (B)
SCL: J3.2, J16.3, J17.3, J21.4, JP3.1 (A), R8.1, U2.36 (IO22), U3.3 (SCL), U11.6 (SCL), U12.4 (SCK), U13.4 (SCK), U15.10 (SCL), U20.3 (SCL), U23.23 (SCL), X2.7 (SCL)
SDA: J3.1, J16.4, J17.4, J21.3, JP4.1 (A), R5.1, U2.31 (IO19), U3.4 (SDA), U11.7 (SDA), U12.3 (SDI), U13.3 (SDI), U15.9 (SDA), U20.4 (SDA), U23.24 (SDA), X2.6 (SDA)
SERVO2: J2.2, U2.26 (IO4), U8.3 (CE), U14.6 (DVC), X3.1 (M0), X4.4 (K-PWRKEY)
SPI_CLK: JP2.1 (A), JP3.3 (B), JP7.1 (A), U2.37 (IO23)
SPI_CLKx: JP7.2 (B), U8.5 (SCK)
SPI_MISO: U2.27 (IO16), U8.7 (MISO), X3.4 (TXD), X4.3 (T-TX)
SPI_MOSI: JP4.3 (B), JP6.1 (A), U2.33 (IO21)
SPI_MOSIx: JP6.2 (B), U8.6 (MOSI), X3.3 (RXD), X4.2 (R-RXD)
SW: C20.2, R20.2, R21.2, SW3.2, TP2.1, U2.4 (SENSOR_VP)
SW_BLUE: J12.51, J12.52, SW1.2
SW_WHITE: J12.53, J12.54, SW5.2
